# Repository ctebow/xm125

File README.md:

# XM125 Teensy Radar Project

This repository contains the files for a custom PCB project that integrates Acconeer's XM125 radar sensor with a Teensy microcontroller.

## Hardware

Here are some pictures of the physical setup.

### Front

### Back

## PCB Schematic

The schematic for the custom PCB is shown below. This board breaks out the necessary connections for the XM125 radar sensor and provides a platform for development with a Teensy.

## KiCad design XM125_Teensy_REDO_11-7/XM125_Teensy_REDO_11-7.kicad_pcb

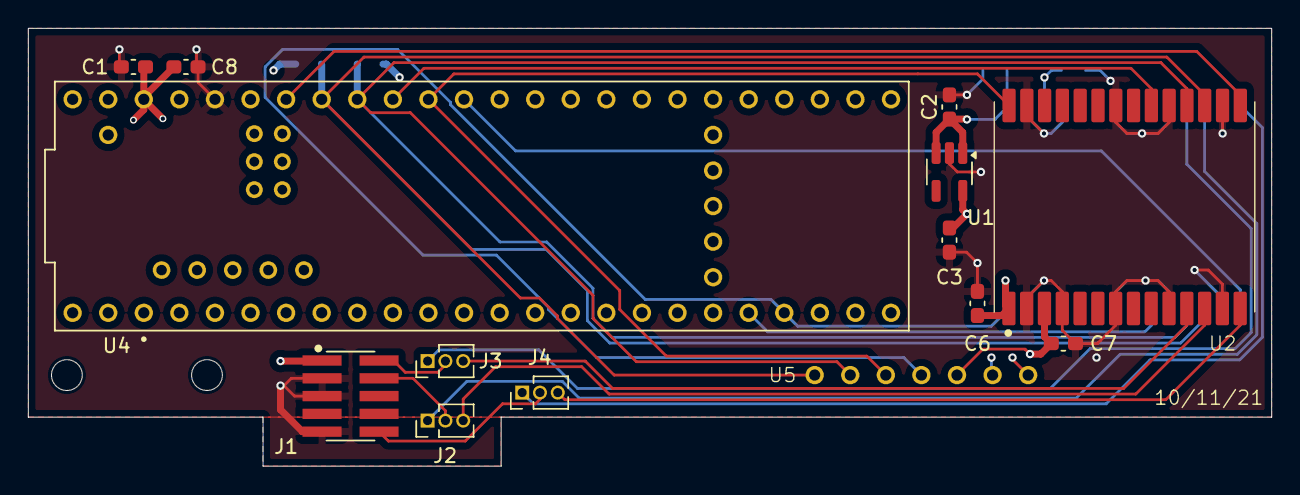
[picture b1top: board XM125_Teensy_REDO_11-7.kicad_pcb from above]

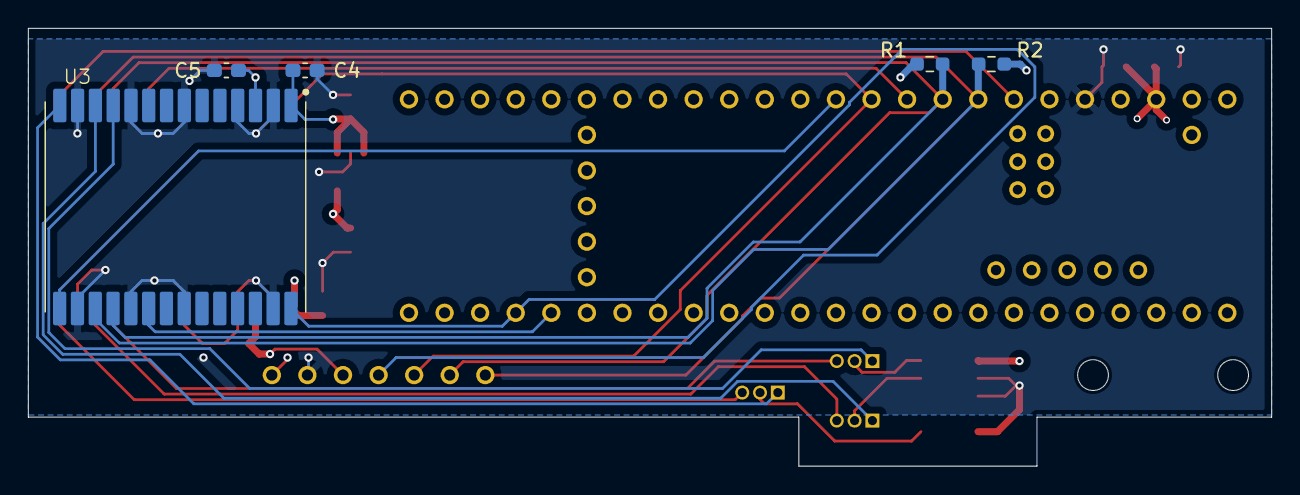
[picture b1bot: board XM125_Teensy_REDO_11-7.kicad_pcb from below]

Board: 4 copper layers, 88.8 x 31.2 mm, 19 parts (5 on the bottom side), 20 nets.

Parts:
C1: 10uF; C_0603_1608Metric_Pad1.08x0.95mm_HandSolder
C2, C3, C4, C5, C6, C7, C8: 0.1uF; C_0603_1608Metric_Pad1.08x0.95mm_HandSolder
J1: Conn_ARM_JTAG_SWD_10; FTS-105-03-L-DV
J2: J_SWD_CLK; PinHeader_1x03_P1.27mm_Vertical
J3: J_SWD_IO; PinHeader_1x03_P1.27mm_Vertical
J4: J_RESET; PinHeader_1x03_P1.27mm_Vertical
R1, R2: 4.7k; R_0603_1608Metric_Pad0.98x0.95mm_HandSolder
U1: TLV713185PDBV; SOT-23-5_HandSoldering
U2, U3: XM125
U4: DEV-16771; MODULE_DEV-16771
U5: Debug

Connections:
+1V8: C3.1, C5.1, C7.1, U1.5 (OUT), U2.3 (1V8), U3.3 (1V8), U5.9
+3V3: C1.1, C2.1, C4.2, C6.2, C8.1, J1.1 (VTref), R1.1, R2.1, U1.1 (IN), U1.3 (EN), U2.1 (3v3), U3.1 (3v3), U4.3.3V_1 (3.3V), U4.3.3V_2 (3.3V), U4.3.3V_3 (3.3V), U5.7
/ADDR1: U3.20 (I2C_ADDR), U4.28 (RX7)
/ADDR2: U2.20 (I2C_ADDR), U4.17 (A3)
/INT1: U3.28 (MCU_INT), U4.29 (TX7), U5.10
/INT2: U2.28 (MCU_INT), U4.16 (A2), U5.11
/RESET: J1.10 (~RESET), J4.2
/RESET1: J4.1, U3.14 (NRESET)
/RESET2: J4.3, U2.14 (NRESET)
/SCL: R2.2, U2.17 (I2C_SCL), U3.17 (I2C_SCL), U4.19 (A5), U5.13
/SDA: R1.2, U2.18 (I2C_SDA), U3.18 (I2C_SDA), U4.18 (A4), U5.12
/SWD_CLK: J1.4 (SWCLK/TCK), J2.2
/SWD_CLK_1: J2.1, U3.12 (SWD_CLK)
/SWD_CLK_2: J2.3, U2.12 (SWD_CLK)
/SWD_IO: J1.2 (SWDIO/TMS), J3.2
/SWD_IO_1: J3.1, U3.11 (SWD_IO)
/SWD_IO_2: J3.3, U2.11 (SWD_IO)
/WAKE1: U3.15 (WAKE_UP), U4.15 (A1)
/WAKE2: U2.15 (WAKE_UP), U4.20 (A6)
GND: C1.2, C2.2, C3.2, C4.1, C5.2, C6.1, C7.2, C8.2, J1.3 (GND), J1.5 (GND), J1.9 (GNDDetect), U1.2 (GND), U2.2 (GND), U2.4 (GND), U2.7 (GND), U2.10 (GND), U2.13 (GND), U2.16 (GND), U2.19 (GND), U2.22 (GND), U2.27 (GND), U3.2 (GND), U3.4 (GND), U3.7 (GND), U3.10 (GND), U3.13 (GND), U3.16 (GND), U3.19 (GND), U3.22 (GND), U3.27 (GND), U4.22 (A8), U5.8

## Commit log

2026-01-27 Add images
2026-01-27 Add schematic image
2026-01-28 New python control script
2026-01-30 Start Distance Benchmarking
2026-01-30 Teensy Scripts
2026-02-02 Refactor in cursor
2026-02-02 Rebase
2026-02-05 Benchmarked back sensor at mm and cm scale
2026-02-06 New dual control script for teensy
2026-02-20 Strength characterization woes
2026-02-24 Figuring things out
2026-03-02 More data taken --> conclude 2.5mm limit
2026-03-04 update benchmarking
2026-03-09 Started doing some dual testing
2026-03-10 Update schematic and dual fitting
2026-03-31 Add new pipeline for capturing raw iq data
2026-05-04 create new data visualization pipeline
2026-05-04 Add data vis pipeline
